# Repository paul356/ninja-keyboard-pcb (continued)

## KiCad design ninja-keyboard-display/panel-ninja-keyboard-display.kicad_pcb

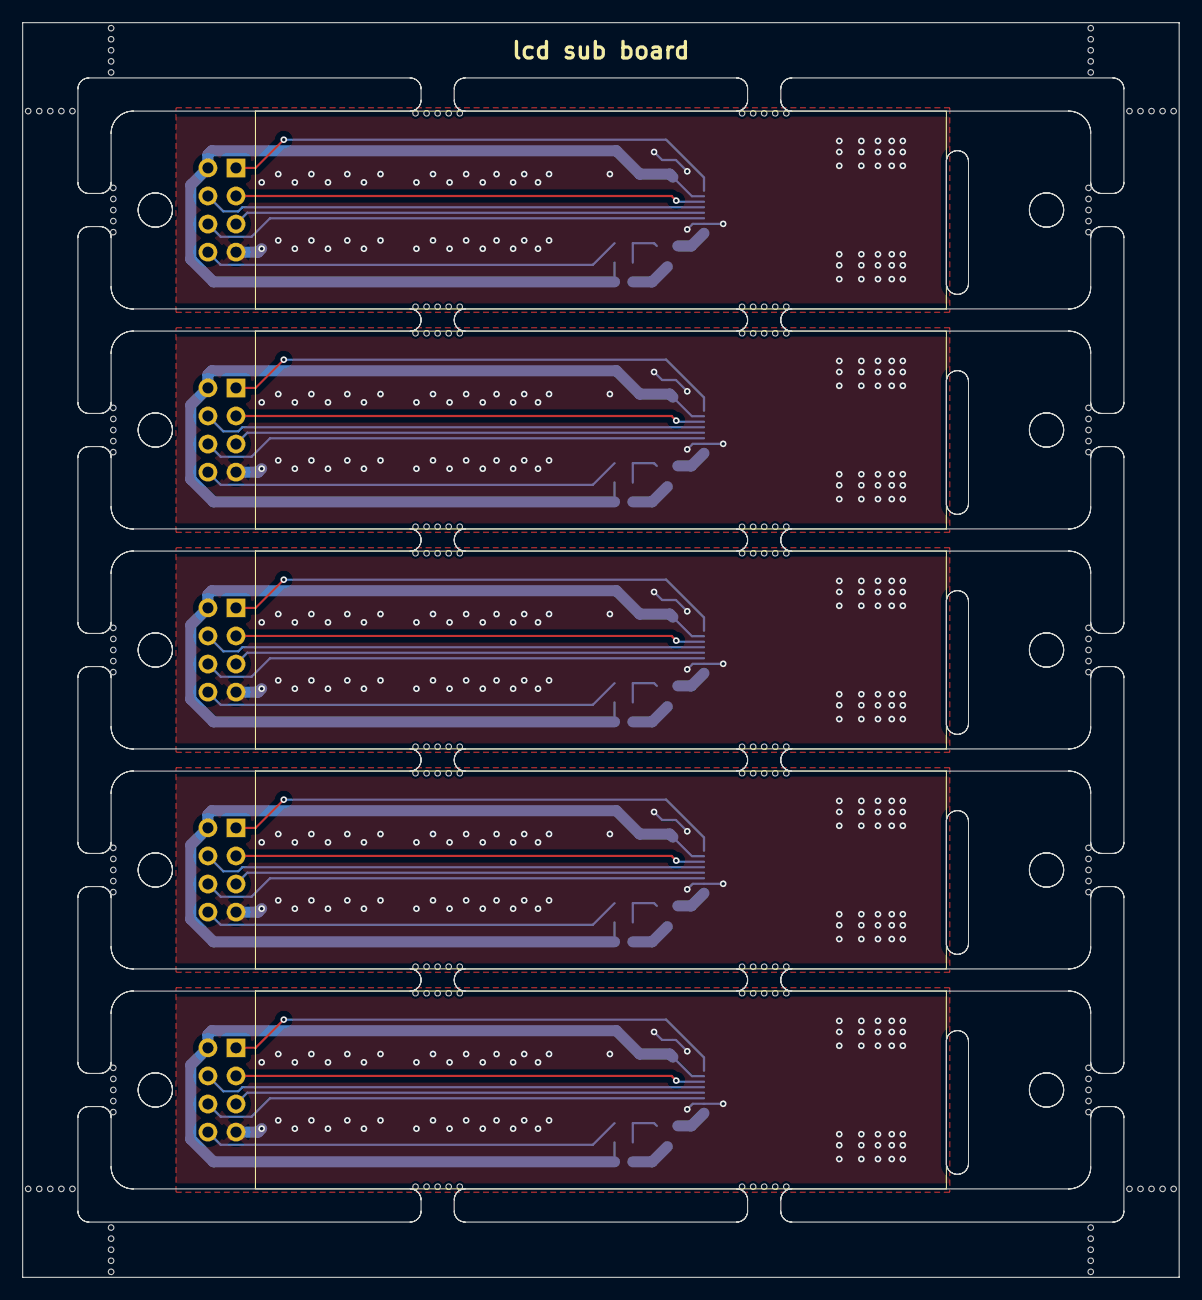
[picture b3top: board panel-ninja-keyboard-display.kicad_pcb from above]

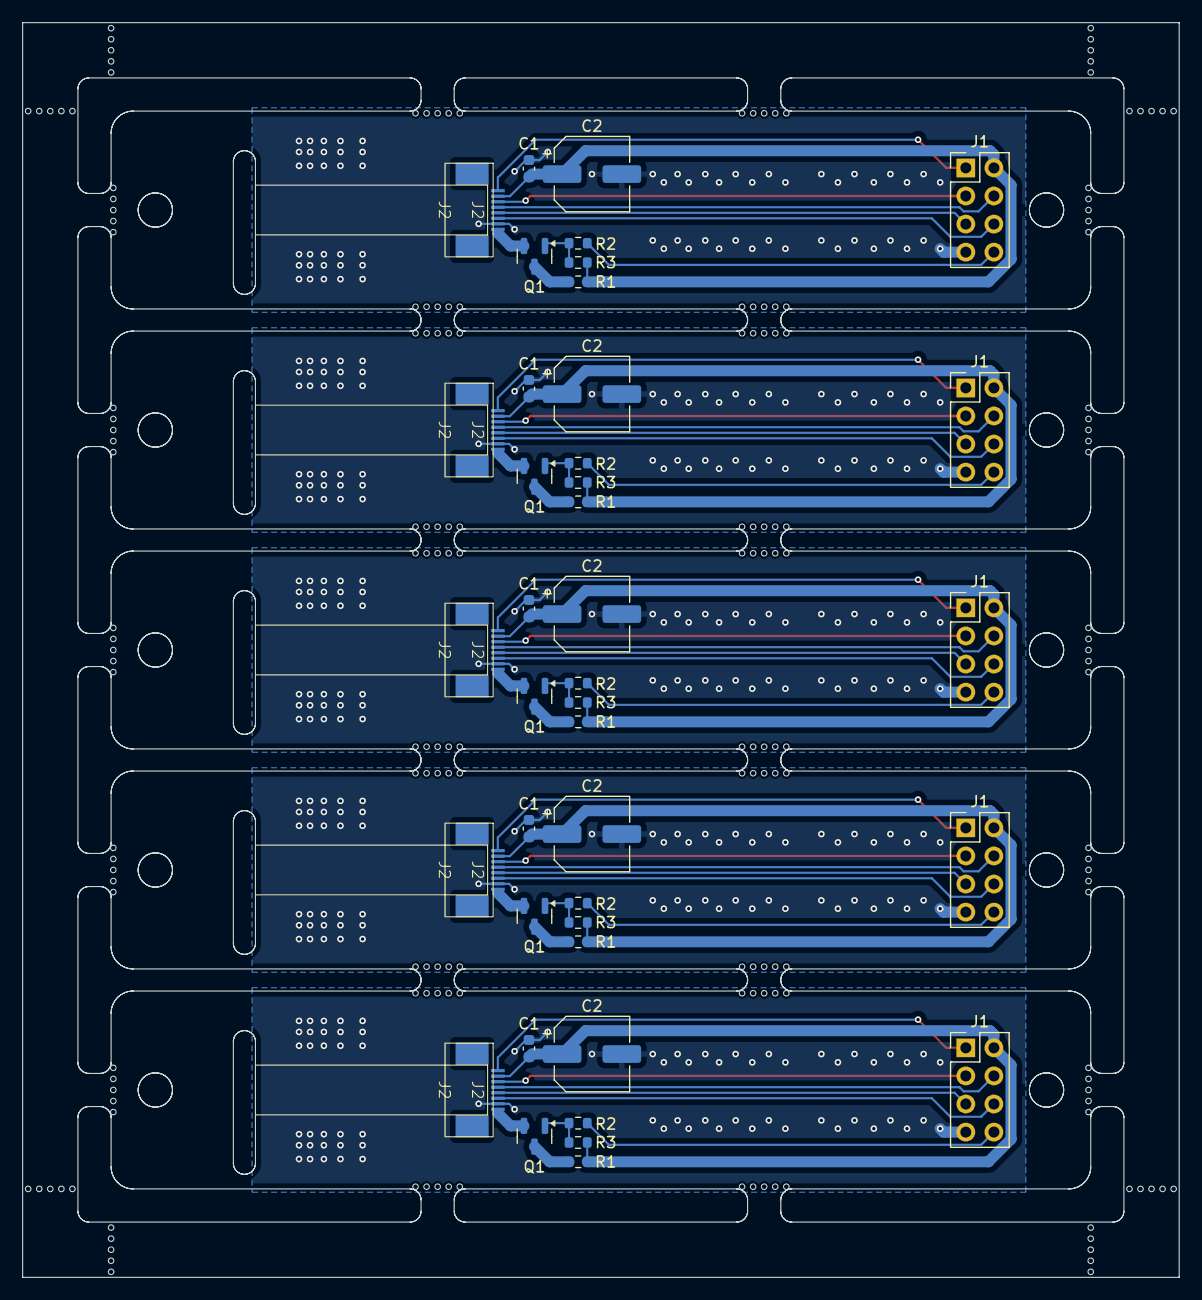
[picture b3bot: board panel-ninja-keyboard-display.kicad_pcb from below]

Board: 2 copper layers, 104.6 x 113.5 mm, 230 parts (40 on the bottom side), 55 nets.

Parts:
C1, C1#2, C1#3, C1#4, C1#5: 0.1uF; C_0603_1608Metric
C2, C2#2, C2#3, C2#4, C2#5: 100uF; CP_Elec_6.3x7.7
J1, J1#2, J1#3, J1#4, J1#5: Conn_02x04_Counter_Clockwise; PinHeader_2x04_P2.54mm_Vertical
J2, J2#2, J2#3, J2#4, J2#5: HanElectricity 1x8 P0.5mm drawer up-side
KiKit_MB_1_1, KiKit_MB_1_2, KiKit_MB_1_3, KiKit_MB_1_4, KiKit_MB_1_5, KiKit_MB_2_1, KiKit_MB_2_2, KiKit_MB_2_3, KiKit_MB_2_4, KiKit_MB_2_5, KiKit_MB_3_1, KiKit_MB_3_2, KiKit_MB_3_3, KiKit_MB_3_4, KiKit_MB_3_5, KiKit_MB_4_1, KiKit_MB_4_2, KiKit_MB_4_3, KiKit_MB_4_4, KiKit_MB_4_5, KiKit_MB_5_1, KiKit_MB_5_2, KiKit_MB_5_3, KiKit_MB_5_4, KiKit_MB_5_5, KiKit_MB_6_1, KiKit_MB_6_2, KiKit_MB_6_3, KiKit_MB_6_4, KiKit_MB_6_5, KiKit_MB_7_1, KiKit_MB_7_2, KiKit_MB_7_3, KiKit_MB_7_4, KiKit_MB_7_5, KiKit_MB_8_1, KiKit_MB_8_2, KiKit_MB_8_3, KiKit_MB_8_4, KiKit_MB_8_5, KiKit_MB_9_1, KiKit_MB_9_2, KiKit_MB_9_3, KiKit_MB_9_4, KiKit_MB_9_5, KiKit_MB_10_1, KiKit_MB_10_2, KiKit_MB_10_3, KiKit_MB_10_4, KiKit_MB_10_5, KiKit_MB_11_1, KiKit_MB_11_2, KiKit_MB_11_3, KiKit_MB_11_4, KiKit_MB_11_5, KiKit_MB_12_1, KiKit_MB_12_2, KiKit_MB_12_3, KiKit_MB_12_4, KiKit_MB_12_5, KiKit_MB_13_1, KiKit_MB_13_2, KiKit_MB_13_3, KiKit_MB_13_4, KiKit_MB_13_5, KiKit_MB_14_1, KiKit_MB_14_2, KiKit_MB_14_3, KiKit_MB_14_4, KiKit_MB_14_5, KiKit_MB_15_1, KiKit_MB_15_2, KiKit_MB_15_3, KiKit_MB_15_4, KiKit_MB_15_5, KiKit_MB_16_1, KiKit_MB_16_2, KiKit_MB_16_3, KiKit_MB_16_4, KiKit_MB_16_5, KiKit_MB_17_1, KiKit_MB_17_2, KiKit_MB_17_3, KiKit_MB_17_4, KiKit_MB_17_5, KiKit_MB_18_1, KiKit_MB_18_2, KiKit_MB_18_3, KiKit_MB_18_4, KiKit_MB_18_5, KiKit_MB_19_1, KiKit_MB_19_2, KiKit_MB_19_3, KiKit_MB_19_4, KiKit_MB_19_5, KiKit_MB_20_1, KiKit_MB_20_2, KiKit_MB_20_3, KiKit_MB_20_4, KiKit_MB_20_5, KiKit_MB_21_1, KiKit_MB_21_2, KiKit_MB_21_3, KiKit_MB_21_4, KiKit_MB_21_5, KiKit_MB_22_1, KiKit_MB_22_2, KiKit_MB_22_3, KiKit_MB_22_4, KiKit_MB_22_5, KiKit_MB_23_1, KiKit_MB_23_2, KiKit_MB_23_3, KiKit_MB_23_4, KiKit_MB_23_5, KiKit_MB_24_1, KiKit_MB_24_2, KiKit_MB_24_3, KiKit_MB_24_4, KiKit_MB_24_5, KiKit_MB_25_1, KiKit_MB_25_2, KiKit_MB_25_3, KiKit_MB_25_4, KiKit_MB_25_5, KiKit_MB_26_1, KiKit_MB_26_2, KiKit_MB_26_3, KiKit_MB_26_4, KiKit_MB_26_5, KiKit_MB_27_1, KiKit_MB_27_2, KiKit_MB_27_3, KiKit_MB_27_4, KiKit_MB_27_5, KiKit_MB_28_1, KiKit_MB_28_2, KiKit_MB_28_3, KiKit_MB_28_4, KiKit_MB_28_5, KiKit_MB_29_1, KiKit_MB_29_2, KiKit_MB_29_3, KiKit_MB_29_4, KiKit_MB_29_5, KiKit_MB_30_1, KiKit_MB_30_2, KiKit_MB_30_3, KiKit_MB_30_4, KiKit_MB_30_5, KiKit_MB_31_2, KiKit_MB_31_3, KiKit_MB_31_4, KiKit_MB_31_5, KiKit_MB_31_6, KiKit_MB_32_2, KiKit_MB_32_3, KiKit_MB_32_4, KiKit_MB_32_5, KiKit_MB_32_6, KiKit_MB_33_2, KiKit_MB_33_3, KiKit_MB_33_4, KiKit_MB_33_5, KiKit_MB_33_6, KiKit_MB_34_2, KiKit_MB_34_3, KiKit_MB_34_4, KiKit_MB_34_5, KiKit_MB_34_6, KiKit_MB_35_2, KiKit_MB_35_3, KiKit_MB_35_4, KiKit_MB_35_5, KiKit_MB_35_6, KiKit_MB_36_2, KiKit_MB_36_3, KiKit_MB_36_4, KiKit_MB_36_5, KiKit_MB_36_6, KiKit_MB_37_2, KiKit_MB_37_3, KiKit_MB_37_4, KiKit_MB_37_5, KiKit_MB_37_6, KiKit_MB_38_2, KiKit_MB_38_3, KiKit_MB_38_4, KiKit_MB_38_5, KiKit_MB_38_6: NPTH
Q1, Q1#2, Q1#3, Q1#4, Q1#5: SS8050; SOT-23
R1, R1#2, R1#3, R1#4, R1#5: 10R; R_0603_1608Metric
R2, R2#2, R2#3, R2#4, R2#5: 1K; R_0603_1608Metric
R3, R3#2, R3#3, R3#4, R3#5: 10K; R_0603_1608Metric

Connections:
Board_0-/3V3: C1#3.2, C2#3.1, J1#2.2, J2.7, R1#3.2, R3.1
Board_0-/LCD_BLK: J1#2.8, R2.1
Board_0-/LCD_CS: J1#2.1, J2.8
Board_0-/LCD_DC: J1#2.5, J2.4
Board_0-/LCD_LEDA: J2.1, Q1#4.2 (E)
Board_0-/LCD_RST: J1#2.6, J2.3
Board_0-/LCD_SCL: J1#2.3, J2.6
Board_0-/LCD_SDA: J1#2.4, J2.5
Board_0-GND: C1#3.1, C2#3.2, J1#2.7, J2.2
Board_0-Net-(Q1-B): Q1#4.1 (B), R2.2, R3.2
Board_0-Net-(Q1-C): Q1#4.3 (C), R1#3.1
Board_1-/3V3: C1#2.2, C2#5.1, J1#5.2, J2#2.7, R1#5.2, R3#3.1
Board_1-/LCD_BLK: J1#5.8, R2#5.1
Board_1-/LCD_CS: J1#5.1, J2#2.8
Board_1-/LCD_DC: J1#5.5, J2#2.4
Board_1-/LCD_LEDA: J2#2.1, Q1#5.2 (E)
Board_1-/LCD_RST: J1#5.6, J2#2.3
Board_1-/LCD_SCL: J1#5.3, J2#2.6
Board_1-/LCD_SDA: J1#5.4, J2#2.5
Board_1-GND: C1#2.1, C2#5.2, J1#5.7, J2#2.2
Board_1-Net-(Q1-B): Q1#5.1 (B), R2#5.2, R3#3.2
Board_1-Net-(Q1-C): Q1#5.3 (C), R1#5.1
Board_2-/3V3: C1#5.2, C2.1, J1#3.2, J2#3.7, R1#4.2, R3#4.1
Board_2-/LCD_BLK: J1#3.8, R2#2.1
Board_2-/LCD_CS: J1#3.1, J2#3.8
Board_2-/LCD_DC: J1#3.5, J2#3.4
Board_2-/LCD_LEDA: J2#3.1, Q1#2.2 (E)
Board_2-/LCD_RST: J1#3.6, J2#3.3
Board_2-/LCD_SCL: J1#3.3, J2#3.6
Board_2-/LCD_SDA: J1#3.4, J2#3.5
Board_2-GND: C1#5.1, C2.2, J1#3.7, J2#3.2
Board_2-Net-(Q1-B): Q1#2.1 (B), R2#2.2, R3#4.2
Board_2-Net-(Q1-C): Q1#2.3 (C), R1#4.1
Board_3-/3V3: C1#4.2, C2#4.1, J1#4.2, J2#4.7, R1.2, R3#5.1
Board_3-/LCD_BLK: J1#4.8, R2#4.1
Board_3-/LCD_CS: J1#4.1, J2#4.8
Board_3-/LCD_DC: J1#4.5, J2#4.4
Board_3-/LCD_LEDA: J2#4.1, Q1#3.2 (E)
Board_3-/LCD_RST: J1#4.6, J2#4.3
Board_3-/LCD_SCL: J1#4.3, J2#4.6
Board_3-/LCD_SDA: J1#4.4, J2#4.5
Board_3-GND: C1#4.1, C2#4.2, J1#4.7, J2#4.2
Board_3-Net-(Q1-B): Q1#3.1 (B), R2#4.2, R3#5.2
Board_3-Net-(Q1-C): Q1#3.3 (C), R1.1
Board_4-/3V3: C1.2, C2#2.1, J1.2, J2#5.7, R1#2.2, R3#2.1
Board_4-/LCD_BLK: J1.8, R2#3.1
Board_4-/LCD_CS: J1.1, J2#5.8
Board_4-/LCD_DC: J1.5, J2#5.4
Board_4-/LCD_LEDA: J2#5.1, Q1.2 (E)
Board_4-/LCD_RST: J1.6, J2#5.3
Board_4-/LCD_SCL: J1.3, J2#5.6
Board_4-/LCD_SDA: J1.4, J2#5.5
Board_4-GND: C1.1, C2#2.2, J1.7, J2#5.2
Board_4-Net-(Q1-B): Q1.1 (B), R2#3.2, R3#2.2
Board_4-Net-(Q1-C): Q1.3 (C), R1#2.1

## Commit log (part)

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2025-04-30 Before removing the tp4056-42 because I can't use AMS1117 with a 3.7v battery
2025-04-30 Lay the components on the board, but haven't connect them with traces
2025-05-01 commit before trying to fix stuck kicad
2025-05-01 use export netlist feature for now
2025-05-05 Before add two inner layers and route with freeroute
2025-05-06 finish all tracks, fix all errors except ones intentionally left
2025-05-06 Add a rotatory encoder and a switch for battery
2025-05-06 Relocate the battery switch
2025-05-14 Remove fuse
2025-06-06 Remove key stablizer holes
2025-06-06 Seperate capacitors and LEDs from the mechanical keys
2025-06-06 position LEDs and capacitors on PCB
2025-06-07 Modify LCD socket pin definition
2025-06-24 Add JLC component serial numbers
2025-06-27 Change board dimension to default 60% layout
2025-07-31 1. Widen tracks for smart leds. 2. Increase output pins for smart leds. 3. Use EC11 for knob switch
2025-07-31 Fix position output of switches and smart leds to correct side
2025-08-23 Fix some LSCS# Numbers
2025-09-13 remove parts belong to the lcd sub board
2025-09-15 Add space and screw holes for LCD sub board
2025-09-15 Add a LCD sub board
2025-09-16 Fix DRC errors: connect zone fields
2025-09-16 save some non-functional changes
2025-09-27 Add a 2 millimeter gap between keys and lcd
2025-11-09 1. Use built in NTC resistors. 2. Correct the position of SL28.
2025-11-10 Add JLC sn to 1x3P 2mm connector
2026-03-20 Save changes for the dev board.
